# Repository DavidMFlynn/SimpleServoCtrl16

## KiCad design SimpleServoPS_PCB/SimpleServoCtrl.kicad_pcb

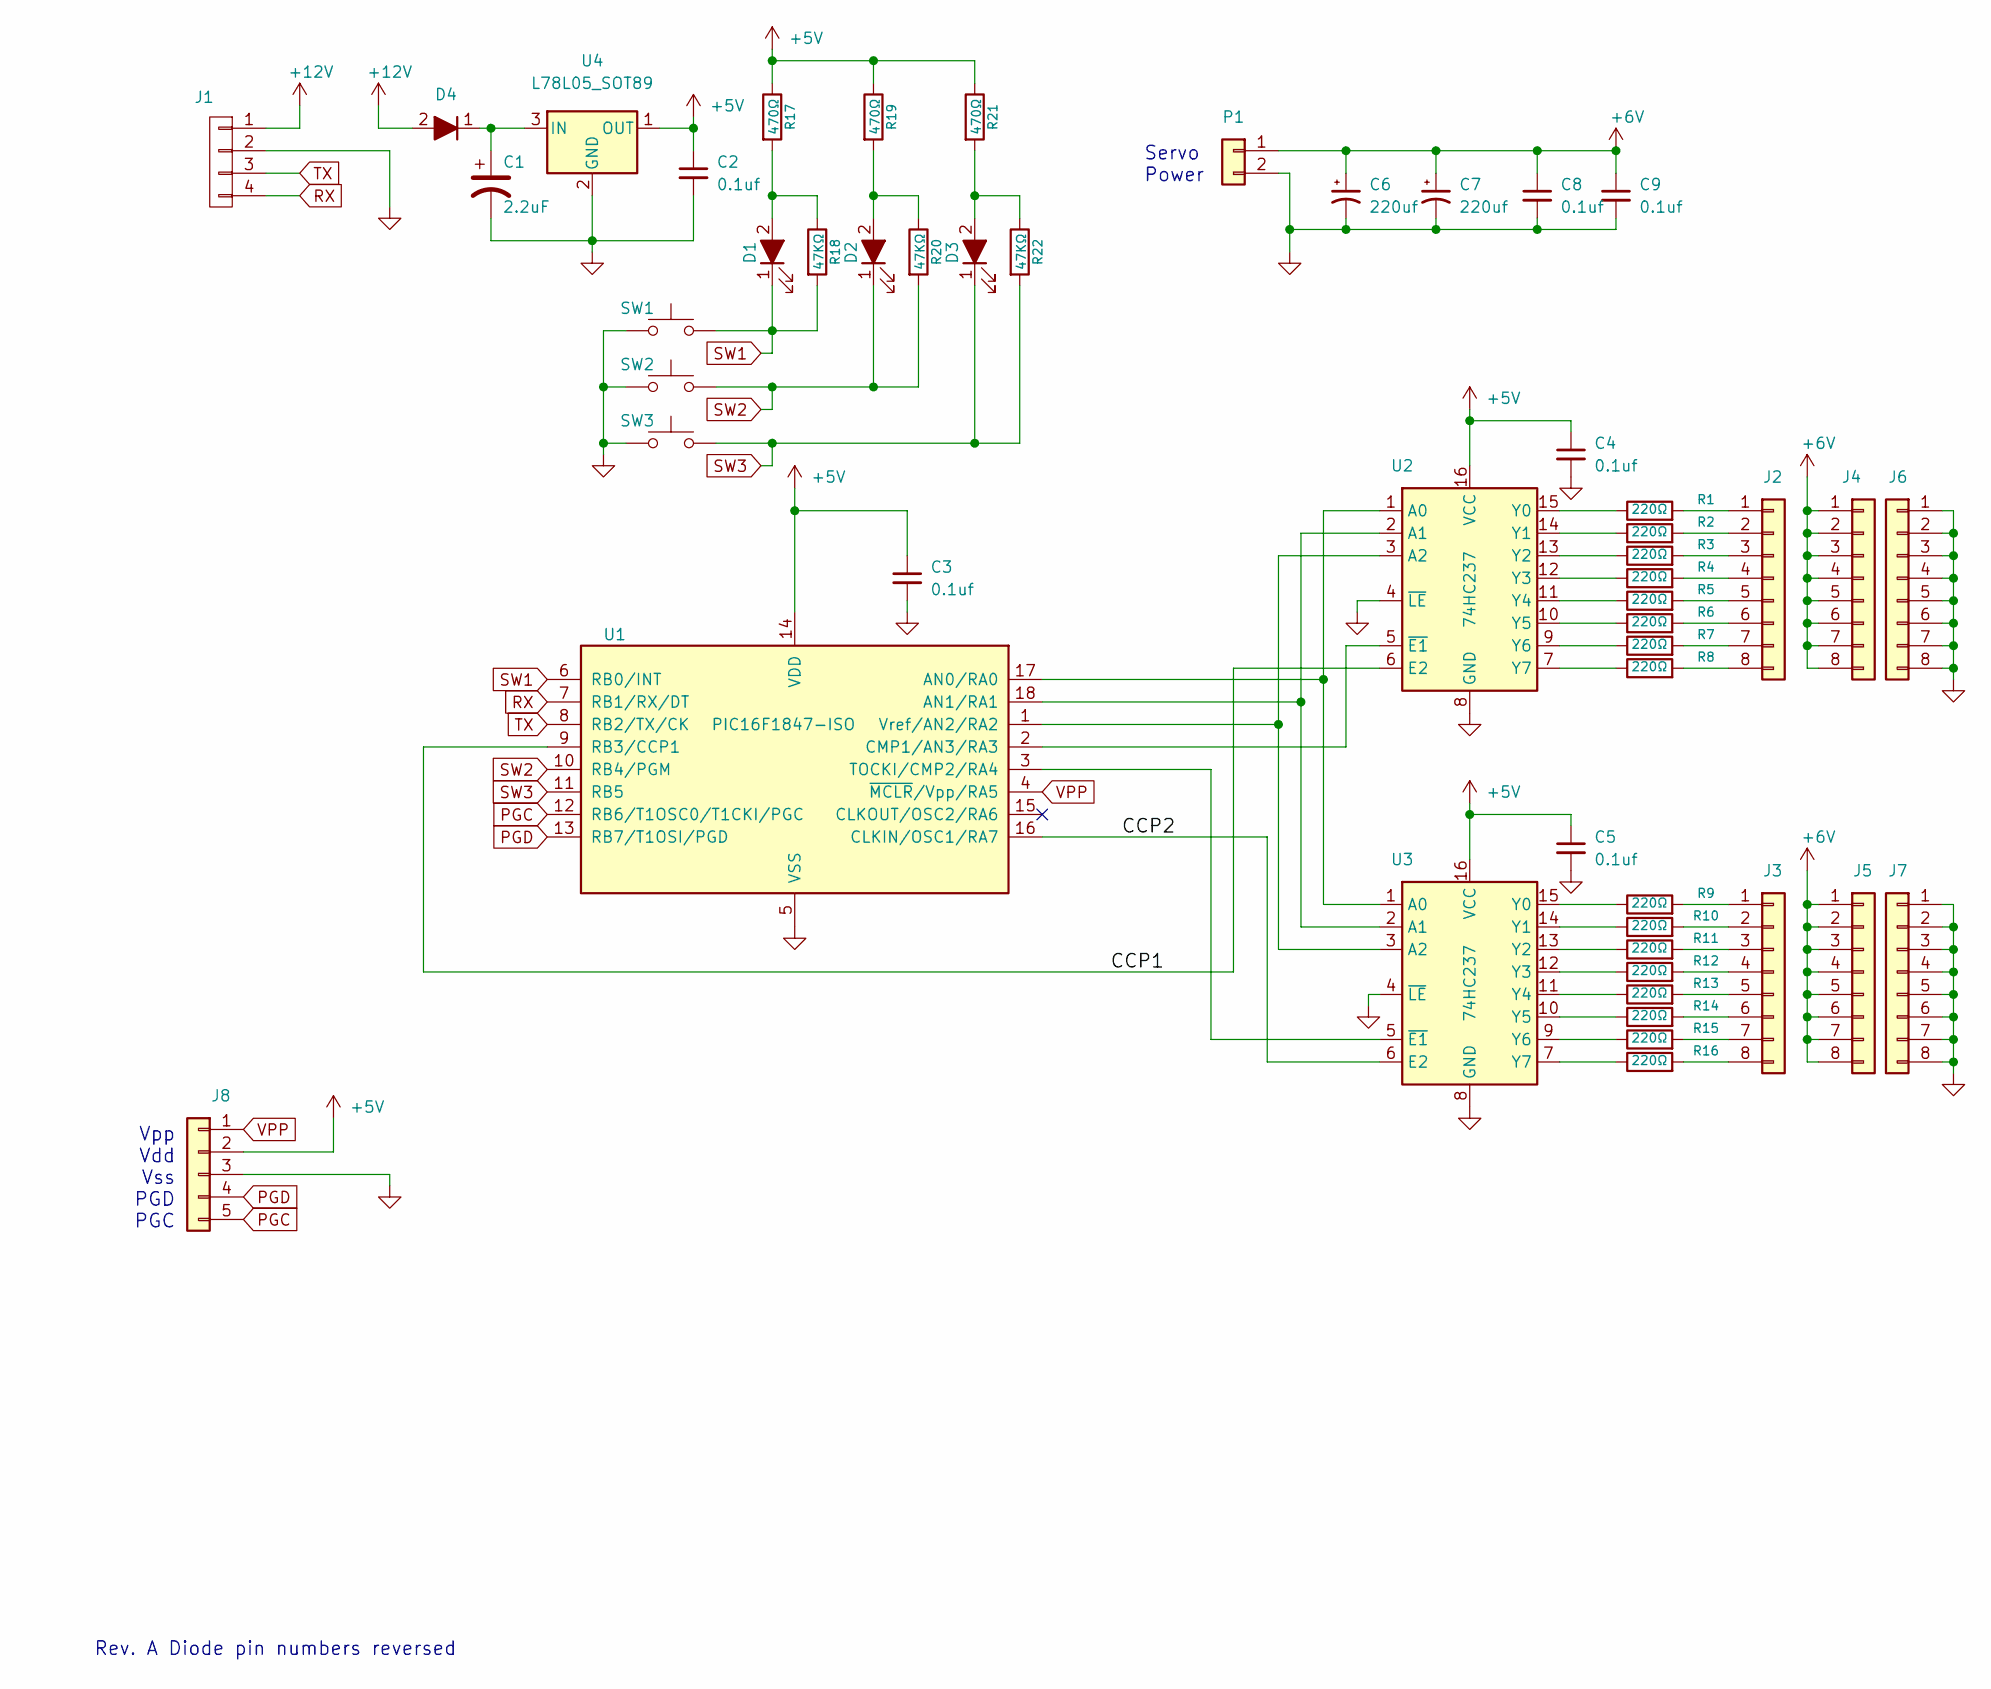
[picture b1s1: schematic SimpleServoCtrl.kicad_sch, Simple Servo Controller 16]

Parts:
C1: 2.2uF; CP_Radial_D5.0mm_P2.00mm
C2, C3, C4, C5, C8, C9: 0.1uf; C_0805_2012Metric_Pad1.18x1.45mm_HandSolder
C6, C7: 220uf; CP_Radial_D10.0mm_P5.00mm
D1, D2, D3: LED
D4: D_Filled
J1: CONN_01X04; Molex_KK-254_AE-6410-04A_1x04_P2.54mm_Vertical
J2, J3, J4, J5, J6, J7: Conn_01x08; PinHeader_1x08_P2.54mm_Vertical
J8: Conn_01x05; PinHeader_1x05_P2.54mm_Vertical
P1: Conn_01x02; PhoenixContact_MSTBVA_2,5_2-G-5,08_1x02_P5.08mm_Vertical
R1, R2, R3, R4, R5, R6, R7, R8, R9, R10, R11, R12, R13, R14, R15, R16: 220Ω; R_0805_2012Metric_Pad1.20x1.40mm_HandSolder
R17, R19, R21: 470Ω; R_0805_2012Metric_Pad1.20x1.40mm_HandSolder
R18, R20, R22: 47KΩ; R_0805_2012Metric_Pad1.20x1.40mm_HandSolder
SW1, SW2, SW3: SW_Push; SW_SPST_FSMSM
U1: PIC16F1847-ISO; SOIC-18W_7.5x11.6mm_P1.27mm
U2, U3: 74HC237; SO-16_5.3x10.2mm_P1.27mm
U4: L78L05_SOT89; SOT-89-3

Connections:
+5V: C2.1, C3.1, C4.1, C5.1, J8.2, R17.1, R19.1, R21.1, U1.14 (VDD), U2.16 (VCC), U3.16 (VCC), U4.1 (OUT)
+6V: C6.1, C7.1, C8.1, C9.1, J4.1, J4.2, J4.3, J4.4, J4.5, J4.6, J4.7, J4.8, J5.1, J5.2, J5.3, J5.4, J5.5, J5.6, J5.7, J5.8, P1.1
+12V: D4.2 (A), J1.1
/CCP1: U1.9 (RB3/CCP1), U2.6 (E2)
/CCP2: U1.16 (CLKIN/OSC1/RA7), U3.6 (E2)
GND: C1.2, C2.2, C3.2, C4.2, C5.2, C6.2, C7.2, C8.2, C9.2, J1.2, J6.1, J6.2, J6.3, J6.4, J6.5, J6.6, J6.7, J6.8, J7.1, J7.2, J7.3, J7.4, J7.5, J7.6, J7.7, J7.8, J8.3, P1.2, SW1.1, SW2.1, SW3.1, U1.5 (VSS), U2.4 (~LE), U2.8 (GND), U3.4 (~LE), U3.8 (GND), U4.2 (GND)
unnamed: C1.1, D4.1 (K), U4.3 (IN)
unnamed: J2.1, R1.2
unnamed: J2.2, R2.2
unnamed: J2.3, R3.2
unnamed: J2.4, R4.2
unnamed: J2.5, R5.2
unnamed: J2.6, R6.2
unnamed: J2.7, R7.2
unnamed: J2.8, R8.2
unnamed: J3.1, R9.2
unnamed: J3.2, R10.2
unnamed: J3.3, R11.2
unnamed: J3.4, R12.2
unnamed: J3.5, R13.2
unnamed: J3.6, R14.2
unnamed: J3.7, R15.2
unnamed: J3.8, R16.2
unnamed: R1.1, U2.15 (Y0)
unnamed: R2.1, U2.14 (Y1)
unnamed: R3.1, U2.13 (Y2)
unnamed: R4.1, U2.12 (Y3)
unnamed: R5.1, U2.11 (Y4)
unnamed: R6.1, U2.10 (Y5)
unnamed: R7.1, U2.9 (Y6)
unnamed: R8.1, U2.7 (Y7)
unnamed: R9.1, U3.15 (Y0)
unnamed: R10.1, U3.14 (Y1)
unnamed: R11.1, U3.13 (Y2)
unnamed: R12.1, U3.12 (Y3)
unnamed: R13.1, U3.11 (Y4)
unnamed: R14.1, U3.10 (Y5)
unnamed: R15.1, U3.9 (Y6)
unnamed: R16.1, U3.7 (Y7)
unnamed: D1.2 (A), R17.2, R18.1
unnamed: D2.2 (A), R19.2, R20.1
unnamed: D3.2 (A), R21.2, R22.1
unnamed: U1.1 (Vref/AN2/RA2), U2.3 (A2), U3.3 (A2)
unnamed: U1.2 (CMP1/AN3/RA3), U2.5 (~E1)
unnamed: U1.3 (TOCKI/CMP2/RA4), U3.5 (~E1)
unnamed: U1.17 (AN0/RA0), U2.1 (A0), U3.1 (A0)
unnamed: U1.18 (AN1/RA1), U2.2 (A1), U3.2 (A1)
PGC: J8.5, U1.12 (RB6/T1OSC0/T1CKI/PGC)
PGD: J8.4, U1.13 (RB7/T1OSI/PGD)
RX: J1.4, U1.7 (RB1/RX/DT)
SW1: D1.1 (K), R18.2, SW1.2, U1.6 (RB0/INT)
SW2: D2.1 (K), R20.2, SW2.2, U1.10 (RB4/PGM)
SW3: D3.1 (K), R22.2, SW3.2, U1.11 (RB5)
TX: J1.3, U1.8 (RB2/TX/CK)
VPP: J8.1, U1.4 (~MCLR~/Vpp/RA5)

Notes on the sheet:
Vpp Vdd Vss PGD PGC
Rev. A Diode pin numbers reversed
Servo Power

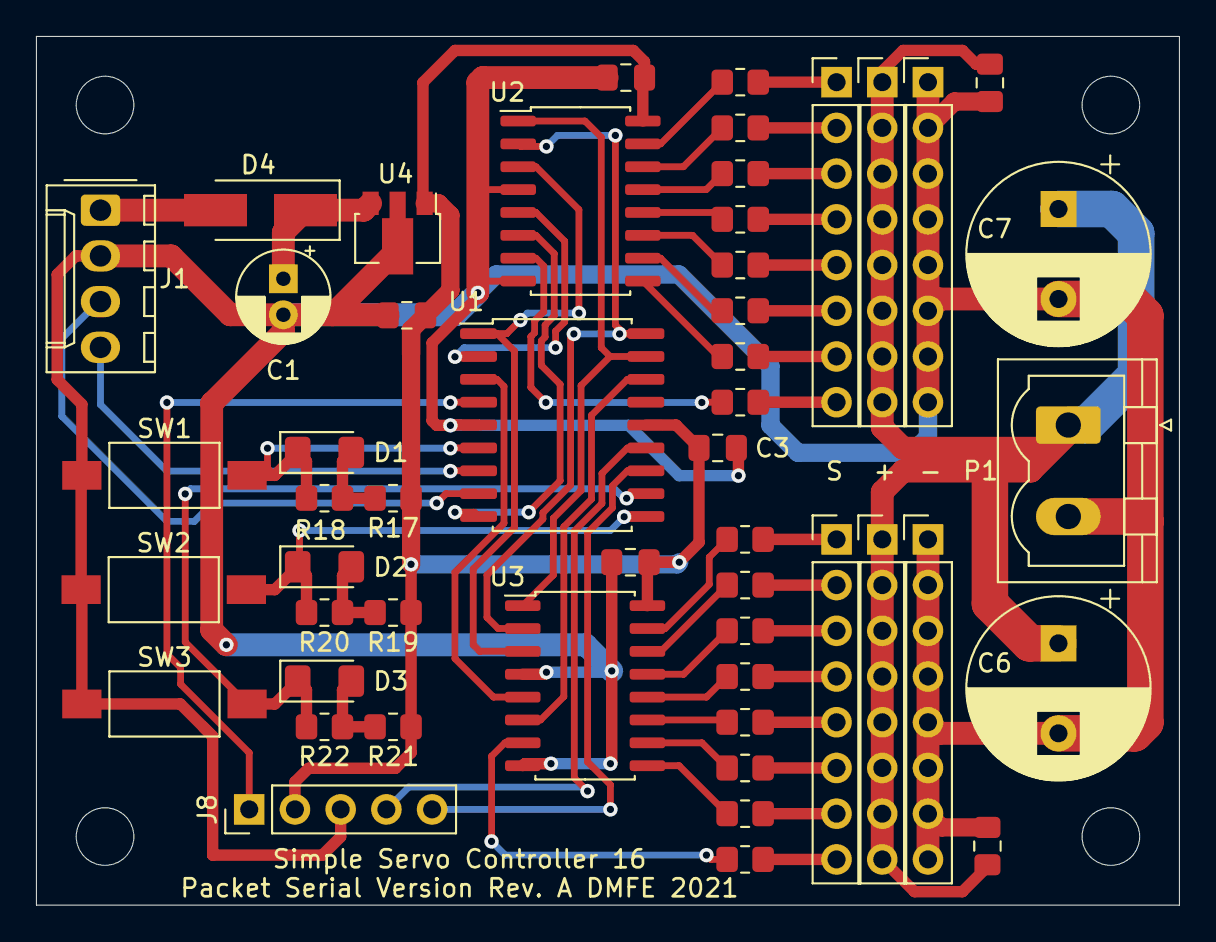
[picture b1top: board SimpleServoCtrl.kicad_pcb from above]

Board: 2 copper layers, 63.5 x 48.3 mm, 55 parts (0 on the bottom side), 55 nets.

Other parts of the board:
H1, H2, H3, H4: MountingHole_3.2mm_M3

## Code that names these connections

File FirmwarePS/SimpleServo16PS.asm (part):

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;====================================================================================================
; PIC16F1847 on SimpleServo16 PCB Packet Serial Version
;
;   Pin 1 (RA2/AN2) Address A2 (output)
;   Pin 2 (RA3/AN3) Enable Servos 0..7 (active low output)
;   Pin 3 (RA4/AN4) Enable Servos 8..15 (active low output)
;   Pin 4 (RA5/MCLR*) Vpp
;   Pin 5 (GND) Ground
;   Pin 6 (RB0) SW1/LED1 (Active Low Input/Output) (System LED)
;   Pin 7 (RB1/AN11/SDA1) RX Data
;   Pin 8 (RB2/AN10/RX)   TX Data 
;   Pin 9 (RB3/CCP1) Pulse output for Servos 0..7
;
;   Pin 10 (RB4/AN8/SLC1) SW2/LED2 (Active Low Input/Output)
;   Pin 11 (RB5/AN7)  SW3/LED3 (Active Low Input/Output)
;   Pin 12 (RB6/AN5/CCP2) ICSPCLK
;   Pin 13 (RB7/AN6) ICSPDAT
;   Pin 14 (Vcc) +5 volts
;   Pin 15 (RA6) N.C.
;   Pin 16 (RA7/CCP2) Pulse output for Servos 8..15
;   Pin 17 (RA0) Address A0 (output)
;   Pin 18 (RA1) Address A1 (output)
;
;====================================================================================================
;
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; INTOSC oscillator: I/O function on CLKIN pin
; WDT disabled
; PWRT disabled
; MCLR/VPP pin function is digital input
; Program memory code protection is disabled
; Data memory code protection is disabled
; Brown-out Reset enabled
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#Define	Servo_A0	LATA,0	;Output
#Define	Servo_A1	LATA,1	;Output
#Define	Servo_A2	LATA,2	;Output
#Define	Enable0_7	LATA,3	;Output RA3
#Define	Enable8_15	LATA,4	;Output RA4
#Define	RA5_In	PORTA,5	;unused, Vpp
#Define	RA6_In	PORTA,6	;unused, n/c
#Define	RA7_Out	PORTA,7	;CCP2 Output
;
Servo_AddrDataMask	EQU	0xF8
;
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#Define	SW1_In	PORTB,0	;SW1/LED1
#Define	RB1_In	PORTB,1	;RX Data
#Define	RB2_In	PORTB,2	;TX Data
#Define	RB3_Out	PORTB,3	;CCP1 Output
#Define	SW2_In	PORTB,4	;SW2/LED2
#Define	SW3_In	PORTB,5	;SW3/LED3
#Define	RB6_In	PORTB,6	;N.C. ICSPCLK
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
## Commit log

2015-11-12 First working code
2015-11-17 Simple test version
    lots more to do
2015-11-20 Worked on I2C Rx/Tx
    Ready to write a master and test the I2C
2021-03-13 Added Packet Serial version
2021-03-30 Added parts list starting f/w
2021-04-01 worked on firmware
2021-04-02 worked on commands
2021-04-02 Commands done
2021-04-02 Rev A
2021-04-03 comments only
2021-04-03 not yet
2021-04-04 working needs more testing
2021-04-06 saving data
2021-04-06 Write while moving?
2021-04-07 began work on sequencer
2021-04-07 Worked on sequencer
2021-04-14 Worked on Seq Cmds
2021-04-15 Sequencer is working

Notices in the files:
SimpleServoPS_PCB/SimpleServoCtrl.kicad_sch:
OSH GPL 2
